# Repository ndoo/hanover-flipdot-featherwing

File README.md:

# hanover-flipdot-featherwing
Hanover Flip-dot Controller for Adafruit HUZZAH32 Feather

## GPIO Assignment

| GPIO | Function                   | Pulldown |
|------|----------------------------|----------|
| 13   | Coil Pulse                 | 10K      |
| 12   | Enable Dot Board 1         | 10K      |
| 27   | Enable Dot Board 2         | 10K      |
| 33   | Enable Dot Board 3         | 10K      |
| 15   | Enable Dot Board 4         | 10K      |
| 32   | Column Advance & Row Reset | 10K      |
| 14   | Column Reset               | 10K      |
| 21   | Row Advance                | 10K      |
| 25   | Dot Set/Unset              | 10K      |

## Acknowledgements

I would be remiss to not credit [Damien Walsh's prior analysis and work on Hanover Flip-dot boards](https://damow.net/fun-with-flip-dot-displays/).

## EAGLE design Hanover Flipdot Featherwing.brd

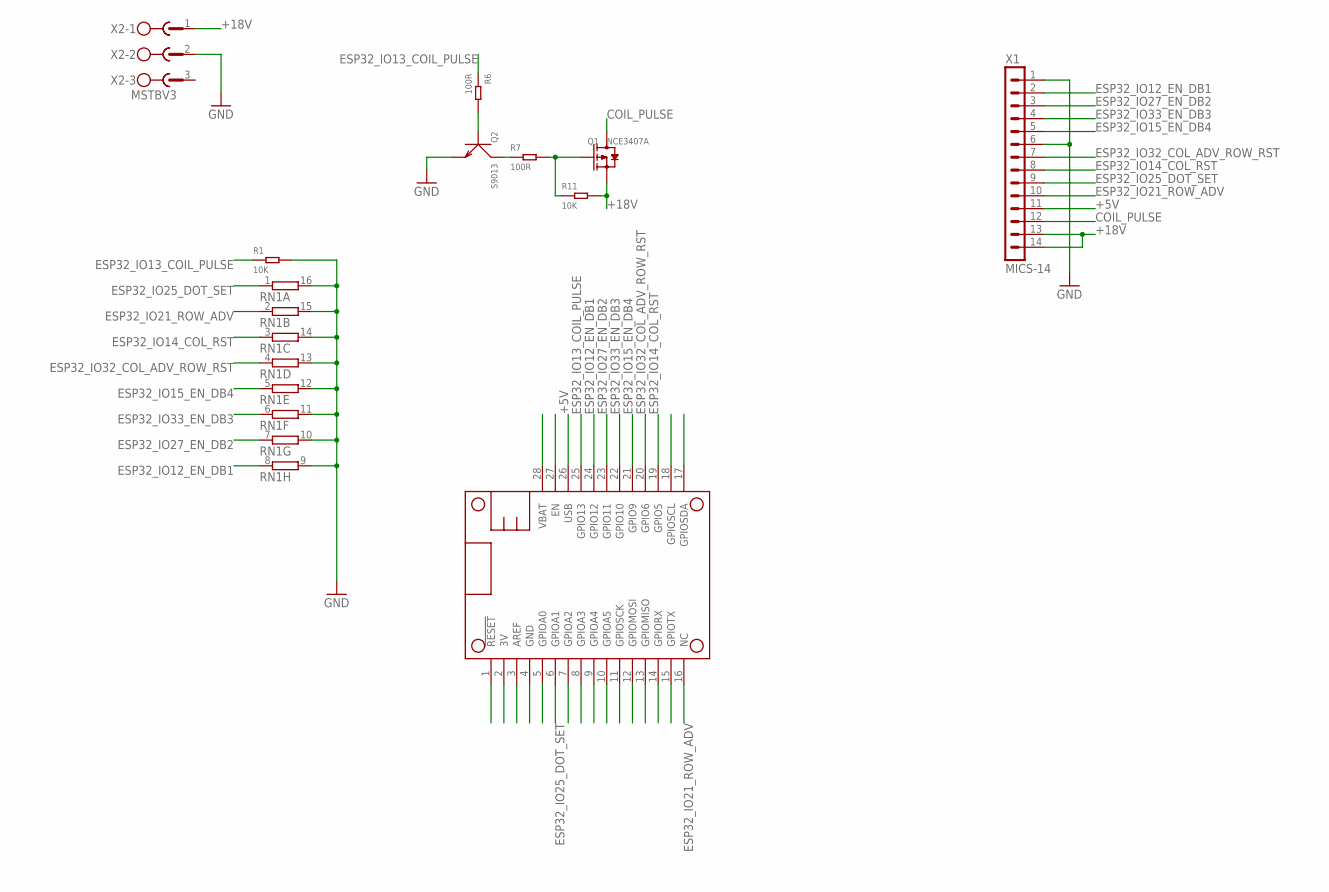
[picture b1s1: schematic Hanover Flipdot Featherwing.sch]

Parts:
MS1: FEATHERWING
Q1: NCE3407A; SOT-23
Q2: S9013; SOT-23
R1, R11: 10K; R0603
R6, R7: 100R; R0603
RN1: 8R-NEXB2HV; EXB2HV
X1: MICS-14
X2: MSTBV3

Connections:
3V: MS1.2 (3V)
+5V: MS1.26 (USB), X1.11
+18V: Q1.2 (S), R11.2, X1.13, X1.14, X2.1
AREF: MS1.3 (AREF)
COIL_PULSE: Q1.3 (D), X1.12
ESP32_IO12_EN_DB1: MS1.24 (GPIO12), RN1.8 (1), X1.2
ESP32_IO13_COIL_PULSE: MS1.25 (GPIO13), R1.1, R6.1
ESP32_IO14_COL_RST: MS1.19 (GPIO5), RN1.3 (1), X1.8
ESP32_IO15_EN_DB4: MS1.21 (GPIO9), RN1.5 (1), X1.5
ESP32_IO21_ROW_ADV: MS1.16 (NC), RN1.2 (1), X1.10
ESP32_IO25_DOT_SET: MS1.6 (GPIOA1), RN1.1, X1.9
ESP32_IO27_EN_DB2: MS1.23 (GPIO11), RN1.7 (1), X1.3
ESP32_IO32_COL_ADV_ROW_RST: MS1.20 (GPIO6), RN1.4 (1), X1.7
ESP32_IO33_EN_DB3: MS1.22 (GPIO10), RN1.6 (1), X1.4
GND: MS1.4 (GND), Q2.2 (E), R1.2, RN1.9 (2), RN1.10 (2), RN1.11 (2), RN1.12 (2), RN1.13 (2), RN1.14 (2), RN1.15 (2), RN1.16 (2), X1.1, X1.6, X2.2
unnamed: Q2.1 (B), R6.2
unnamed: Q1.1 (G), R7.2, R11.1
unnamed: Q2.3 (C), R7.1
VBAT: MS1.28 (VBAT)

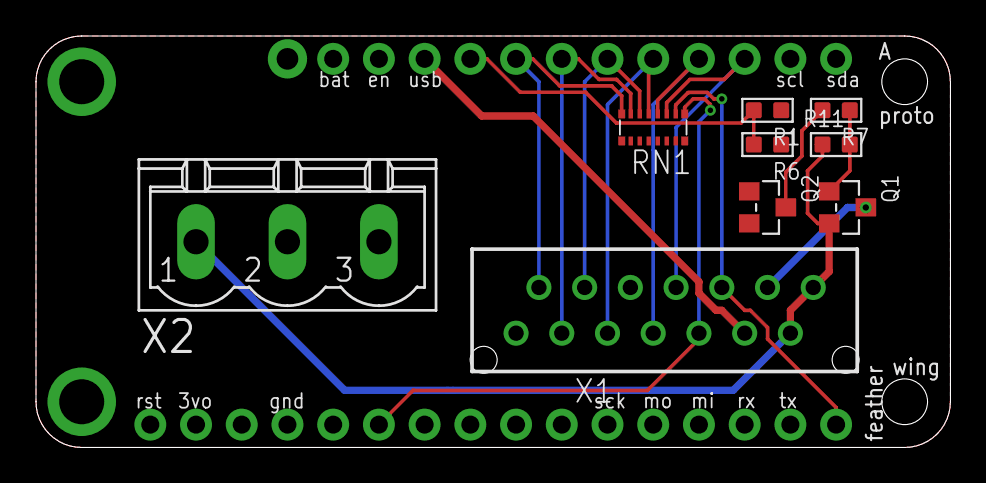
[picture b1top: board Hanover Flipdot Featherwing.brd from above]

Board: 2 copper layers, 50.8 x 22.9 mm, 10 parts (0 on the bottom side), 16 nets.

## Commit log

2021-04-15 Add initial schematic and board; to-do: 18V to 5V DC-DC
2021-04-15 Update README.md with GPIO assignment and acknowledgements
